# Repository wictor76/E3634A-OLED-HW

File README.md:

# HP/Agilent E3634A OLED display to replace old VFD

Big thanks to qu1ck!
See [Original design](https://github.com/openscopeproject/HP34401a-OLED-HW) for more information.

Original HP 34401A design was made for different OLED display. This is modified for different display pinout 
and to have USB connector pointing downwards, since I don't want to make hole to front panel display. 
Input power is also taken from front panel voltage regulator.
This board could be used also in 34401A and other PSUs using similar front panel design. 

This board was designed in KiCad 5 and uses exclusively standard KiCad libraries.

# Schematic

# Board

# BOM

[Interactive BOM](https://htmlpreview.github.io/?https://github.com/wictor76/E3634A-OLED-HW/master/bom/ibom.html)

# OLED

OLED display needs to be configured for parallel data access. This display was initially configured
 for 4 wire SPI, so R18 resistor was moved to R17 to enable parallel 80XX mode.

See following image to locate resistors:

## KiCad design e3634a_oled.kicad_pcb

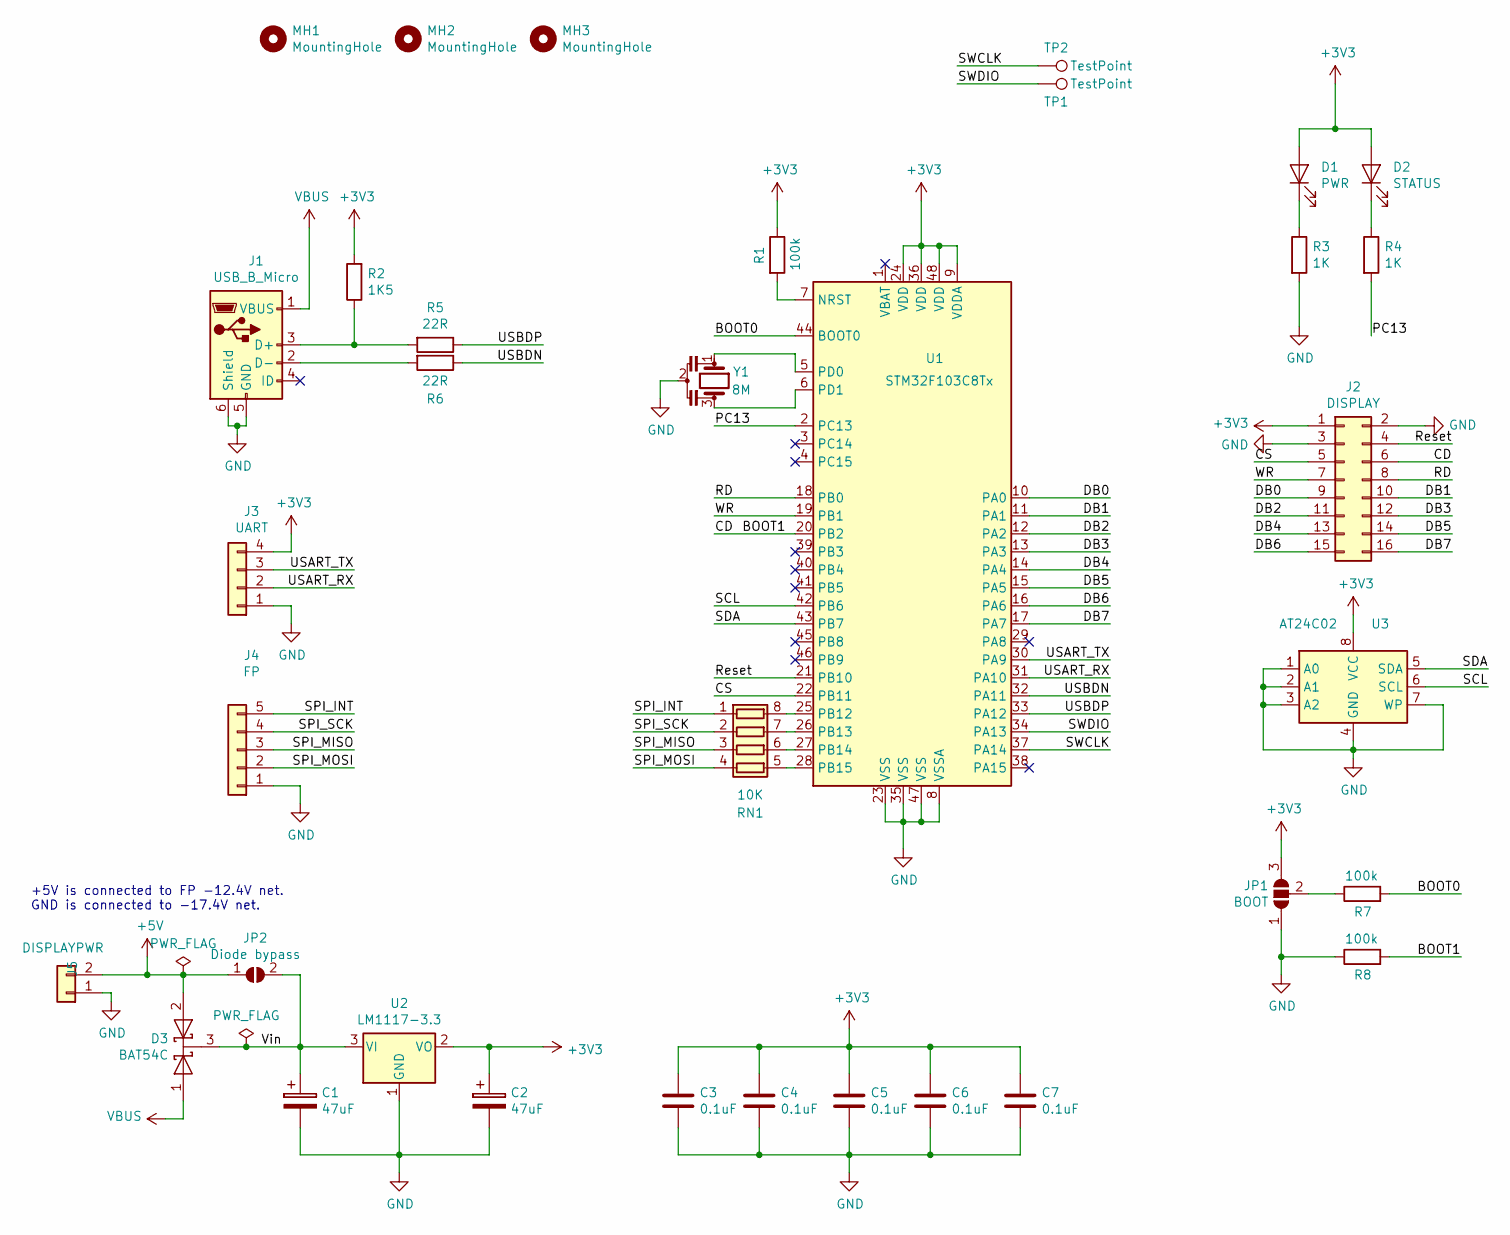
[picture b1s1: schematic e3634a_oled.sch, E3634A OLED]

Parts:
C1, C2: 47uF; CP_EIA-3528-21_Kemet-B_Pad1.50x2.35mm_HandSolder
C3, C4, C5, C6, C7: 0.1uF; C_0603_1608Metric
D1: PWR; LED_0805_2012Metric
D2: STATUS; LED_0805_2012Metric
D3: BAT54C; SOT-23
J1: USB_B_Micro; USB_Micro-B_Molex_47346-0001
J2: DISPLAY; PinHeader_2x08_P2.54mm_Vertical
J3: UART; PinHeader_1x04_P2.54mm_Vertical
J4: FP; PinHeader_1x05_P2.54mm_Vertical
J5: DISPLAYPWR; PinHeader_1x02_P2.54mm_Vertical
JP1: BOOT; SolderJumper-3_P1.3mm_Open_RoundedPad1.0x1.5mm
JP2: Diode bypass; SolderJumper-2_P1.3mm_Open_RoundedPad1.0x1.5mm
MH1, MH2, MH3: MountingHole; MountingHole_3.2mm_M3_ISO14580
R1, R7, R8: 100k; R_0805_2012Metric
R2: 1K5; R_0805_2012Metric
R3, R4: 1K; R_0805_2012Metric
R5, R6: 22R; R_0805_2012Metric
RN1: 10K; R_Array_Convex_4x0603
TP1, TP2: TestPoint; TestPoint_THTPad_D1.5mm_Drill0.7mm
U1: STM32F103C8Tx; LQFP-48_7x7mm_P0.5mm
U2: LM1117-3.3; SOT-223-3_TabPin2
U3: AT24C02; SOIC-8_3.9x4.9mm_P1.27mm
Y1: 8M; Resonator_SMD_muRata_CSTxExxV-3Pin_3.0x1.1mm

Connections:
+3V3: C2.1, C3.1, C4.1, C5.1, C6.1, C7.1, D1.2 (A), D2.2 (A), J2.1, J3.4, JP1.3 (B), R1.1, R2.2, U1.9 (VDDA), U1.24 (VDD), U1.36 (VDD), U1.48 (VDD), U2.2 (VO), U3.8 (VCC)
+5V: D3.2 (A), J5.2, JP2.1 (A)
/BOOT0: R7.2, U1.44 (BOOT0)
/BOOT1: J2.6, R8.2, U1.20 (PB2)
/CS: J2.5, U1.22 (PB11)
/DB0: J2.9, U1.10 (PA0)
/DB1: J2.10, U1.11 (PA1)
/DB2: J2.11, U1.12 (PA2)
/DB3: J2.12, U1.13 (PA3)
/DB4: J2.13, U1.14 (PA4)
/DB5: J2.14, U1.15 (PA5)
/DB6: J2.15, U1.16 (PA6)
/DB7: J2.16, U1.17 (PA7)
/PC13: R4.2, U1.2 (PC13)
/RD: J2.8, U1.18 (PB0)
/Reset: J2.4, U1.21 (PB10)
/SCL: U1.42 (PB6), U3.6 (SCL)
/SDA: U1.43 (PB7), U3.5 (SDA)
/SPI_INT: J4.5, RN1.1 (R1.1)
/SPI_MISO: J4.3, RN1.3 (R3.1)
/SPI_MOSI: J4.2, RN1.4 (R4.1)
/SPI_SCK: J4.4, RN1.2 (R2.1)
/SWCLK: TP2.1, U1.37 (PA14)
/SWDIO: TP1.1, U1.34 (PA13)
/USART_RX: J3.2, U1.31 (PA10)
/USART_TX: J3.3, U1.30 (PA9)
/USBDN: R6.1, U1.32 (PA11)
/USBDP: R5.1, U1.33 (PA12)
/Vin: C1.1, D3.3 (K), JP2.2 (B), U2.3 (VI)
/WR: J2.7, U1.19 (PB1)
GND: C1.2, C2.2, C3.2, C4.2, C5.2, C6.2, C7.2, J1.5 (GND), J1.6 (Shield), J2.2, J2.3, J3.1, J4.1, J5.1, JP1.1 (A), R3.2, R8.1, U1.8 (VSSA), U1.23 (VSS), U1.35 (VSS), U1.47 (VSS), U2.1 (GND), U3.1 (A0), U3.2 (A1), U3.3 (A2), U3.4 (GND), U3.7 (WP), Y1.2
unnamed: D1.1 (K), R3.1
unnamed: D2.1 (K), R4.1
unnamed: J1.2 (D-), R6.2
unnamed: J1.3 (D+), R2.1, R5.2
unnamed: JP1.2 (C), R7.1
unnamed: R1.2, U1.7 (NRST)
unnamed: RN1.5 (R4.2), U1.28 (PB15)
unnamed: RN1.6 (R3.2), U1.27 (PB14)
unnamed: RN1.7 (R2.2), U1.26 (PB13)
unnamed: RN1.8 (R1.2), U1.25 (PB12)
unnamed: U1.5 (PD0), Y1.1
unnamed: U1.6 (PD1), Y1.3
VBUS: D3.1 (A), J1.1 (VBUS)

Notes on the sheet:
+5V is connected to FP -12.4V net. GND is connected to -17.4V net.

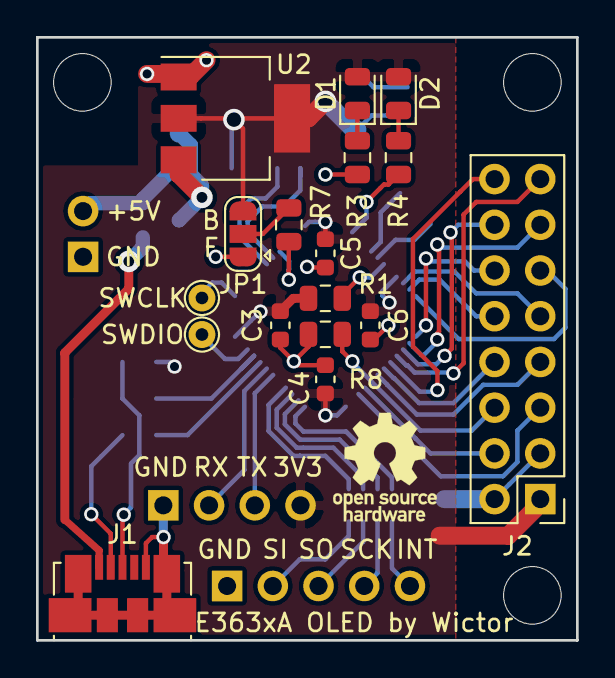
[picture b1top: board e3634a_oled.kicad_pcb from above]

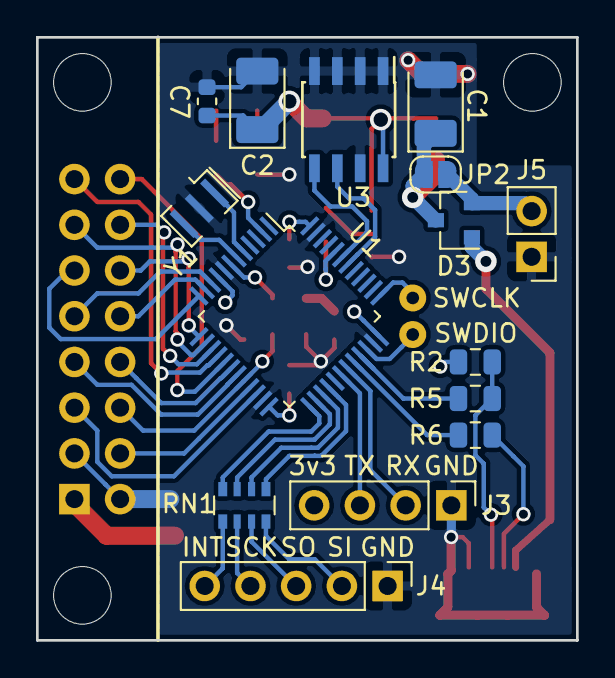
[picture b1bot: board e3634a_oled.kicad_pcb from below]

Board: 2 copper layers, 30.0 x 33.5 mm, 35 parts (15 on the bottom side), 44 nets.

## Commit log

2019-02-22 Modified design for different display panel
2019-02-22 add schematic
2019-02-22 add schema to readme
2019-02-22 add pcb images
2019-02-22 remove dot from header
2019-02-22 add bom
2019-02-22 link to bom
2019-02-22 fix link
2019-02-22 trying to fix link
2019-02-22 add gerbers for elecrow
2019-02-24 add info about OLED display
2019-02-24 use separate folder for images

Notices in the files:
e3634a_oled.kicad_pcb:
Licensed under CERN Open Hardware Licence v1.2
